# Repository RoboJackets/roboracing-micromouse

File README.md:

# Welcome to RoboRacing Micromouse
## What is Micromouse?
Micromouse is RoboRacing's primary project. Members are split into teams of 2-3 to build a brand new bot from scratch. This repository stores the code for RoboRacing's primary competitive bot. 

> Watch a detailed overview of the competition by the Veritasium YouTube Channel

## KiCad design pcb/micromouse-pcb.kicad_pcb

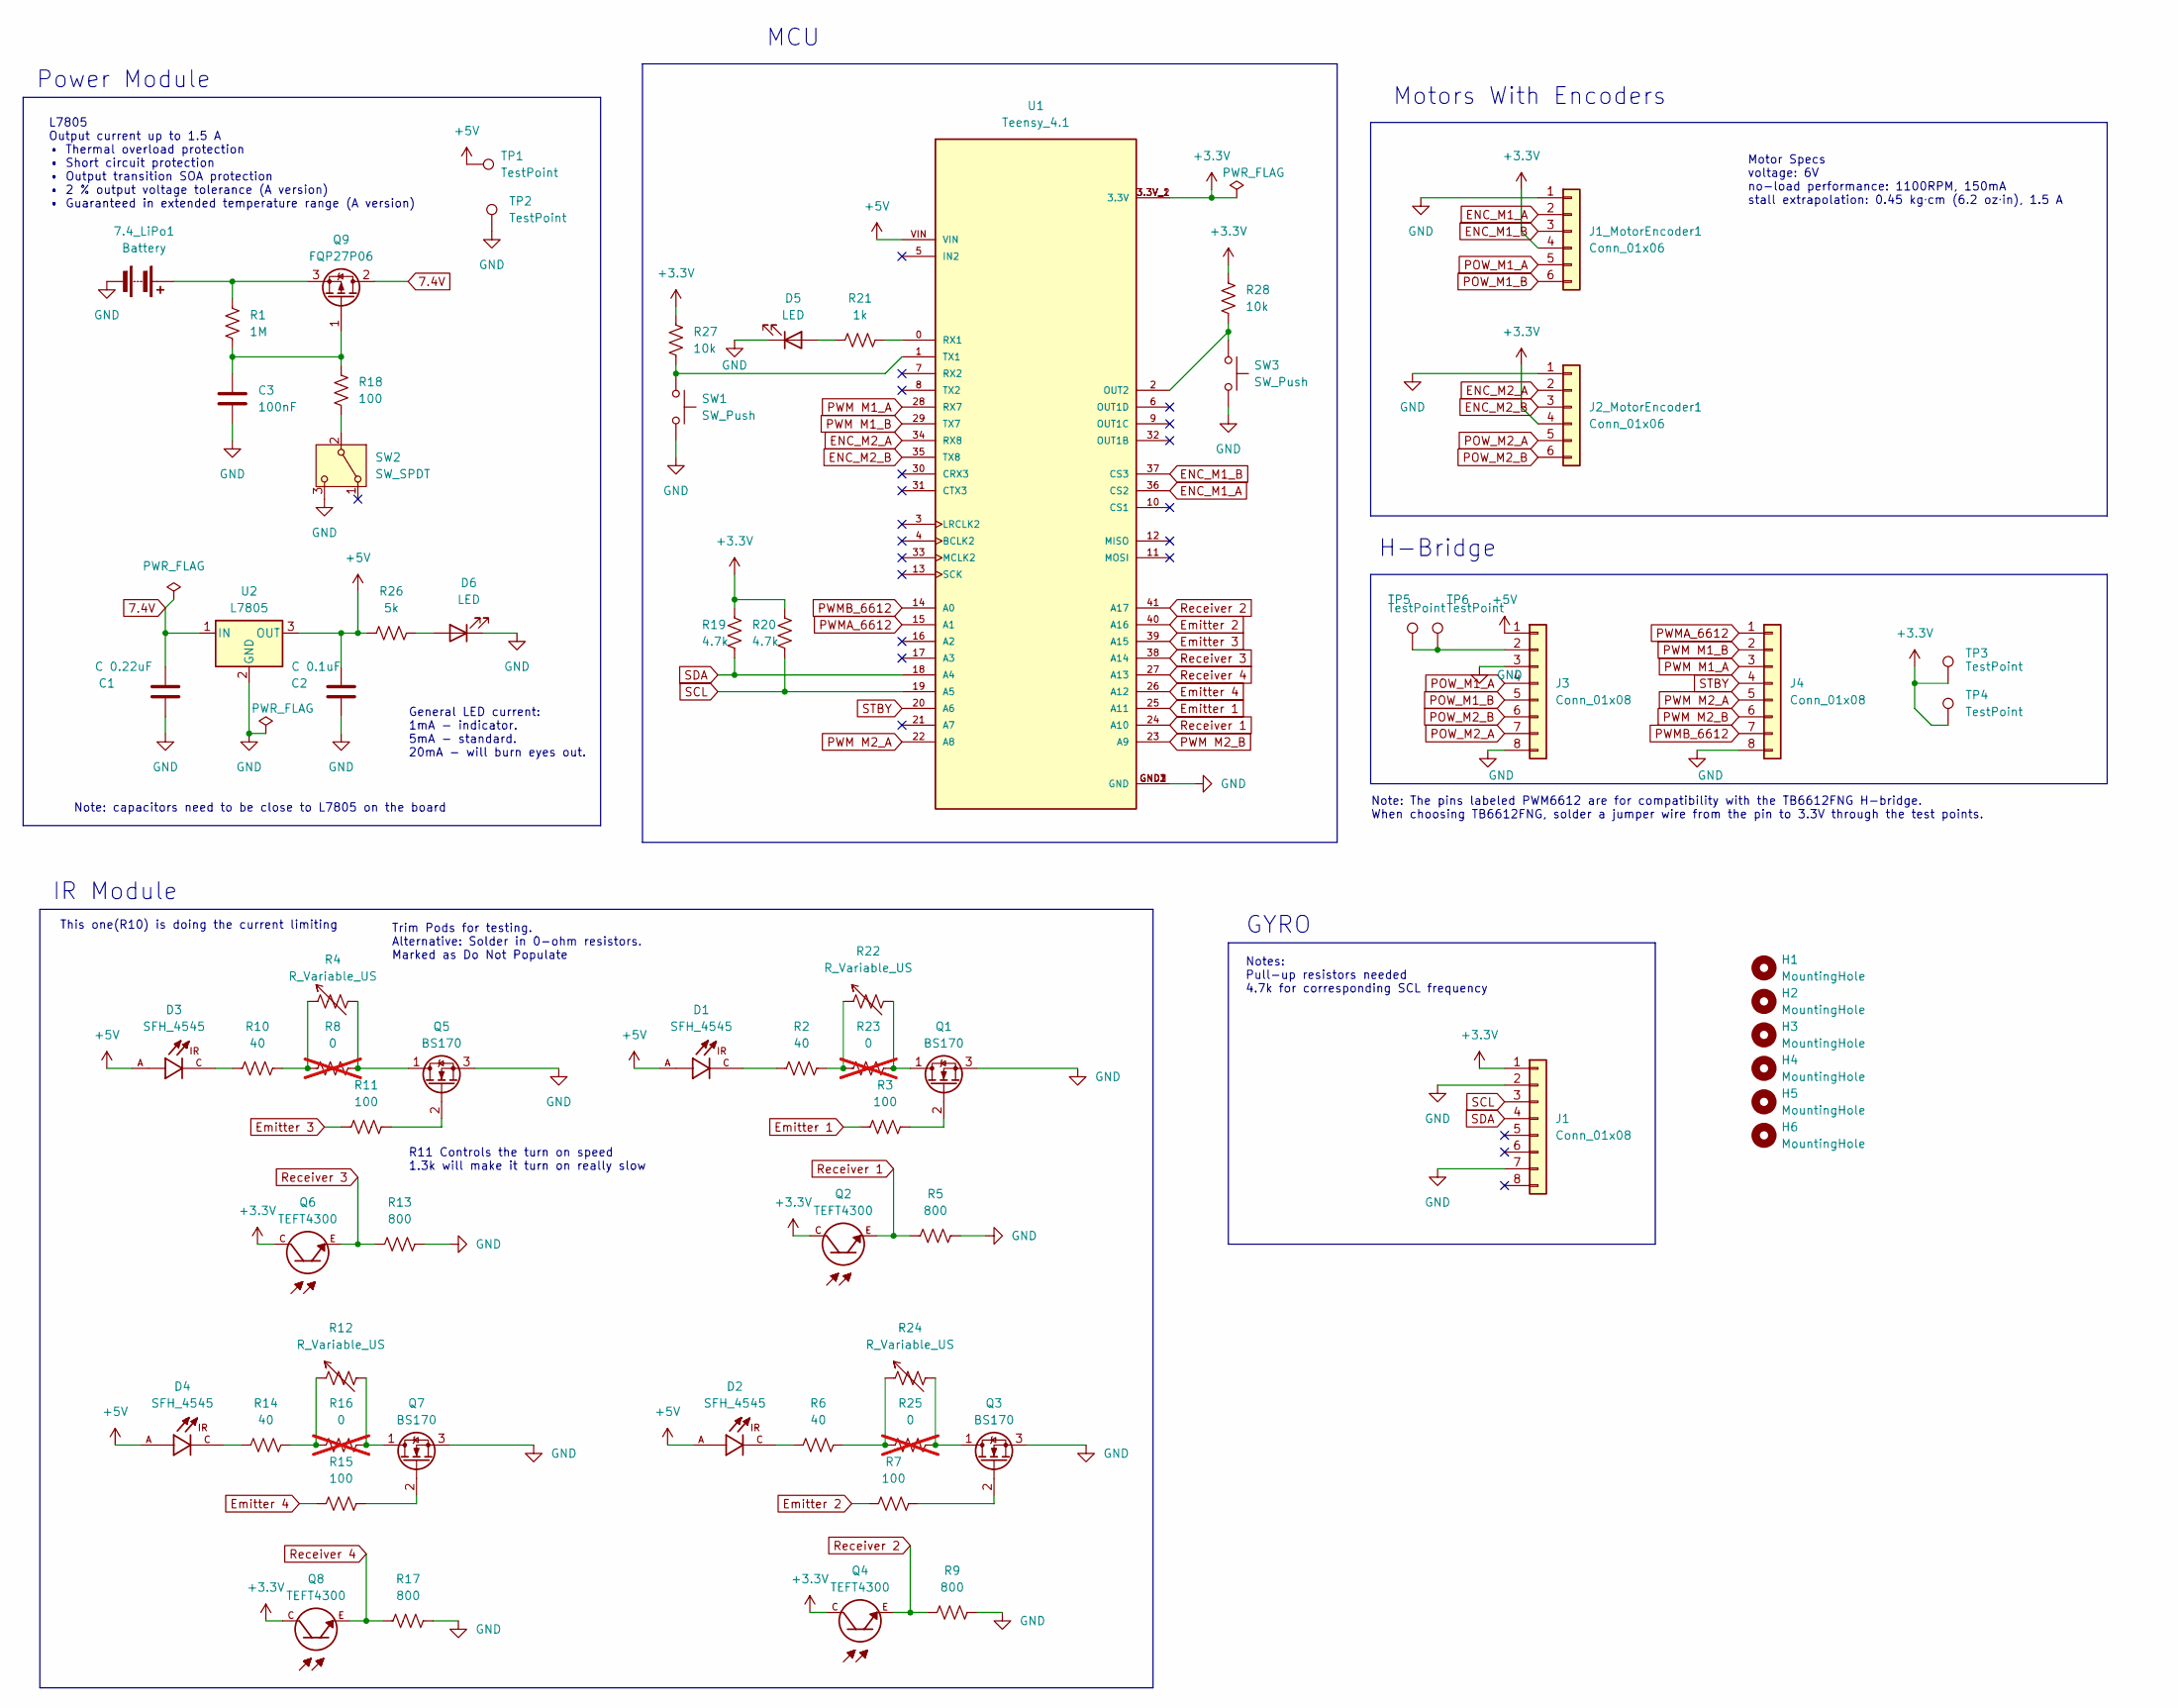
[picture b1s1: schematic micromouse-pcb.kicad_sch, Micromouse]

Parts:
7.4_LiPo1: Battery; JST_PH_B2B-PH-K_1x02_P2.00mm_Vertical
C1: C 0.22uF; C_1206_3216Metric_Pad1.33x1.80mm_HandSolder
C2: C 0.1uF; C_1206_3216Metric_Pad1.33x1.80mm_HandSolder
C3: 100nF; C_1206_3216Metric_Pad1.33x1.80mm_HandSolder
D1, D2, D3, D4: SFH_4545; DIO_SFH_4545_copy; PARTREV 1.5
D5, D6: LED; LED_1206_3216Metric_Pad1.42x1.75mm_HandSolder
H1, H2, H3, H4, H5, H6: MountingHole; MountingHole_4.3mm_M4
J1, J3, J4: Conn_01x08; PinSocket_1x08_P2.54mm_Vertical
J1_MotorEncoder1, J2_MotorEncoder1: Conn_01x06; PinSocket_1x06_P2.54mm_Vertical
Q1, Q3, Q5, Q7: BS170; TO-92_Inline
Q2, Q4, Q6, Q8: TEFT4300; XDCR_TEFT4300
Q9: FQP27P06; TO-220-3_Vertical
R1: 1M; R_1206_3216Metric_Pad1.30x1.75mm_HandSolder
R2, R6, R10, R14: 40; R_1206_3216Metric_Pad1.30x1.75mm_HandSolder
R3, R7, R11, R15, R18: 100; R_1206_3216Metric_Pad1.30x1.75mm_HandSolder
R4, R12, R22, R24: R_Variable_US; TRIM_PV36W203C01B00
R5, R9, R13, R17: 800; R_1206_3216Metric_Pad1.30x1.75mm_HandSolder
R8, R16, R23, R25: 0; R_1206_3216Metric_Pad1.30x1.75mm_HandSolder; not fitted
R19, R20: 4.7k; R_1206_3216Metric_Pad1.30x1.75mm_HandSolder
R21: 1k; R_1206_3216Metric_Pad1.30x1.75mm_HandSolder
R26: 5k; R_1206_3216Metric_Pad1.30x1.75mm_HandSolder
R27, R28: 10k; R_1206_3216Metric_Pad1.30x1.75mm_HandSolder
SW1, SW3: SW_Push; SW_SPST_B3SL-1002P
SW2: SW_SPDT; SW_Slide_SPDT_Angled_CK_OS102011MA1Q
TP1, TP2, TP3, TP4, TP5, TP6: TestPoint; TestPoint_THTPad_D2.0mm_Drill1.0mm
U1: Teensy_4.1; Teensy4.1_LessHoles; PARTREV 4.1
U2: L7805; TO-220-3_Vertical

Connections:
7.4V: C1.1, Q9.2 (D), U2.1 (IN)
+3.3V: J1.1, J1_MotorEncoder1.4, J2_MotorEncoder1.4, Q2.C, Q4.C, Q6.C, Q8.C, R19.1, R20.1, R27.1, R28.1, TP3.1, TP4.1, U1.3.3V_1 (3.3V), U1.3.3V_2 (3.3V)
+5V: C2.2, D1.A, D2.A, D3.A, D4.A, J3.1, R26.1, TP1.1, U1.VIN, U2.3 (OUT)
ENC_M1_A: J1_MotorEncoder1.2, U1.36 (CS2)
ENC_M1_B: J1_MotorEncoder1.3, U1.37 (CS3)
ENC_M2_A: J2_MotorEncoder1.2, U1.34 (RX8)
ENC_M2_B: J2_MotorEncoder1.3, U1.35 (TX8)
Emitter 1: R3.1, U1.25 (A11)
Emitter 2: R7.1, U1.40 (A16)
Emitter 3: R11.1, U1.39 (A15)
Emitter 4: R15.1, U1.26 (A12)
GND: 7.4_LiPo1.2 (-), C1.2, C2.1, C3.2, D5.1 (K), D6.1 (K), J1.2, J1.7, J1_MotorEncoder1.1, J2_MotorEncoder1.1, J3.3, J3.8, J4.8, Q1.3 (S), Q3.3 (S), Q5.3 (S), Q7.3 (S), R5.2, R9.2, R13.2, R17.2, SW1.2, SW2.3 (C), SW3.2, TP2.1, U1.GND1 (GND), U1.GND2 (GND), U1.GND3 (GND), U2.2 (GND)
unnamed: 7.4_LiPo1.1 (+), Q9.3 (S), R1.1
unnamed: D1.C, R2.1
unnamed: D2.C, R6.1
unnamed: D3.C, R10.1
unnamed: D4.C, R14.1
unnamed: D5.2 (A), R21.1
unnamed: D6.2 (A), R26.2
unnamed: J3.2, TP5.1, TP6.1
unnamed: Q1.1 (D), R22.2, R23.2
unnamed: Q1.2 (G), R3.2
unnamed: Q3.1 (D), R24.2, R25.2
unnamed: Q3.2 (G), R7.2
unnamed: Q5.1 (D), R4.2, R8.2
unnamed: Q5.2 (G), R11.2
unnamed: Q7.1 (D), R12.2, R16.2
unnamed: Q7.2 (G), R15.2
unnamed: C3.1, Q9.1 (G), R1.2, R18.1
unnamed: R2.2, R22.1, R23.1
unnamed: R4.1, R8.1, R10.2
unnamed: R12.1, R14.2, R16.1
unnamed: R6.2, R24.1, R25.1
unnamed: R18.2, SW2.2 (B)
unnamed: R28.2, SW3.1, U1.2 (OUT2)
unnamed: R21.2, U1.0 (RX1)
unnamed: R27.2, SW1.1, U1.1 (TX1)
POW_M1_A: J1_MotorEncoder1.5, J3.4
POW_M1_B: J1_MotorEncoder1.6, J3.5
POW_M2_A: J2_MotorEncoder1.5, J3.7
POW_M2_B: J2_MotorEncoder1.6, J3.6
PWM M1_A: J4.3, U1.28 (RX7)
PWM M1_B: J4.2, U1.29 (TX7)
PWM M2_A: J4.5, U1.22 (A8)
PWM M2_B: J4.6, U1.23 (A9)
PWMA_6612: J4.1, U1.15 (A1)
PWMB_6612: J4.7, U1.14 (A0)
Receiver 1: Q2.E, R5.1, U1.24 (A10)
Receiver 2: Q4.E, R9.1, U1.41 (A17)
Receiver 3: Q6.E, R13.1, U1.38 (A14)
Receiver 4: Q8.E, R17.1, U1.27 (A13)
SCL: J1.3, R20.2, U1.19 (A5)
SDA: J1.4, R19.2, U1.18 (A4)
STBY: J4.4, U1.20 (A6)

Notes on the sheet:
Trim Pods for testing. Alternative: Solder in 0-ohm resistors. Marked as Do Not Populate
Note: capacitors need to be close to L7805 on the board
General LED current: 1mA - indicator. 5mA - standard. 20mA - will burn eyes out.
GYRO
H-Bridge
This one(R10) is doing the current limiting
R11 Controls the turn on speed 1.3k will make it turn on really slow
Notes: Pull-up resistors needed 4.7k for corresponding SCL frequency
Power Module
IR Module
MCU
Motor Specs voltage: 6V no-load performance: 1100RPM, 150mA stall extrapolation: 0.45 kg⋅cm (6.2 oz⋅in), 1.5 A
Note: The pins labeled PWM6612 are for compatibility with the TB6612FNG H-bridge. When choosing TB6612FNG, solder a jumper wire from the pin to 3.3V through the test points.
Motors With Encoders
L7805 Output current up to 1.5 A • Thermal overload protection • Short circuit protection • Output transition SOA protection • 2 % output voltage tolerance (A version) • Guaranteed in extended temperature range (A version)

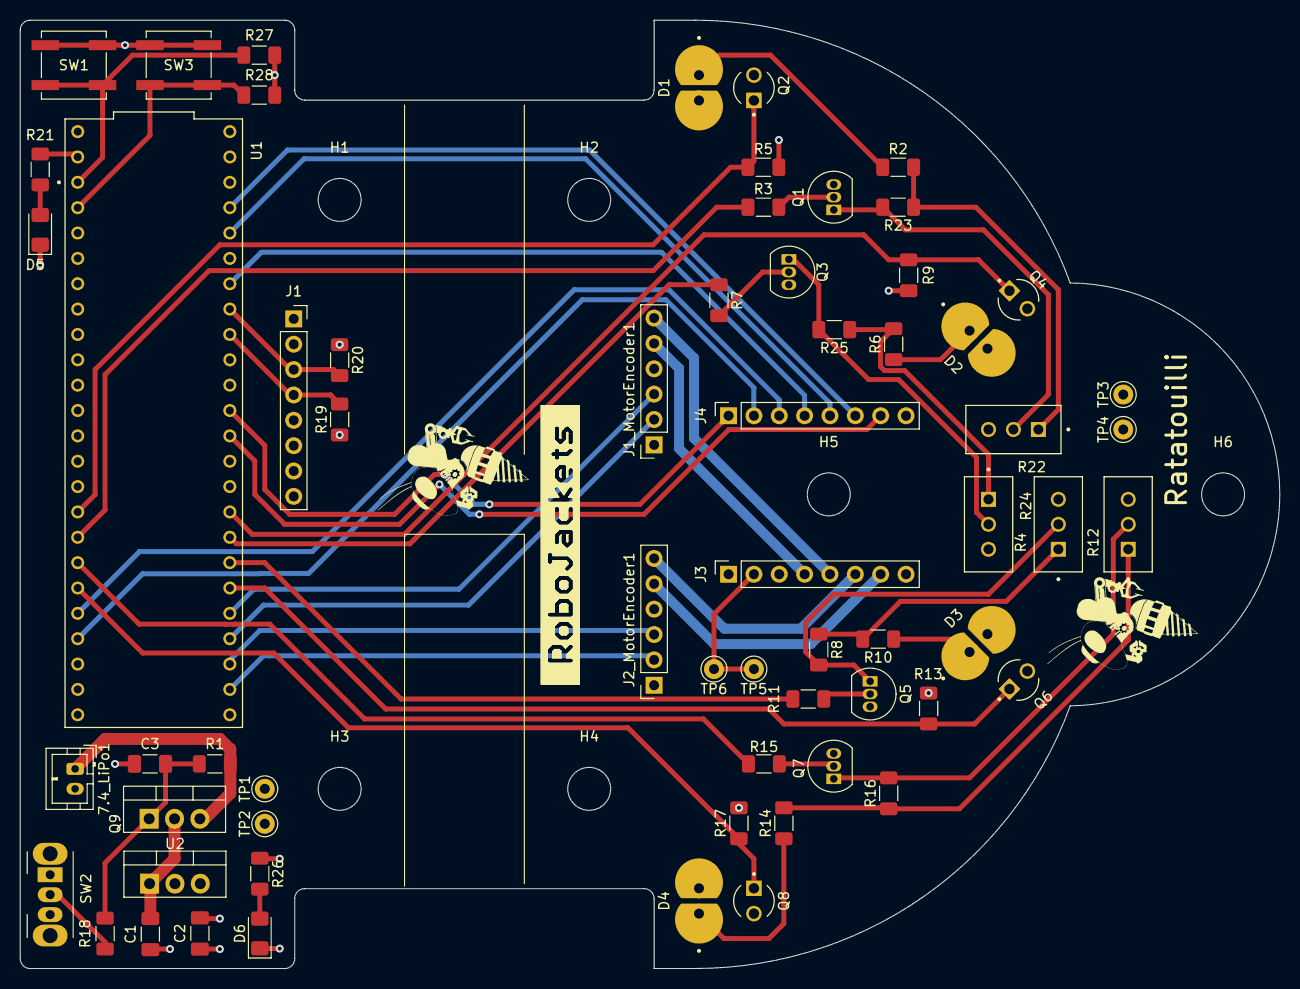
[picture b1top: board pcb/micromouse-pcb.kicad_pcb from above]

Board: 4 copper layers, 126.2 x 95.0 mm, 69 parts (0 on the bottom side), 54 nets.

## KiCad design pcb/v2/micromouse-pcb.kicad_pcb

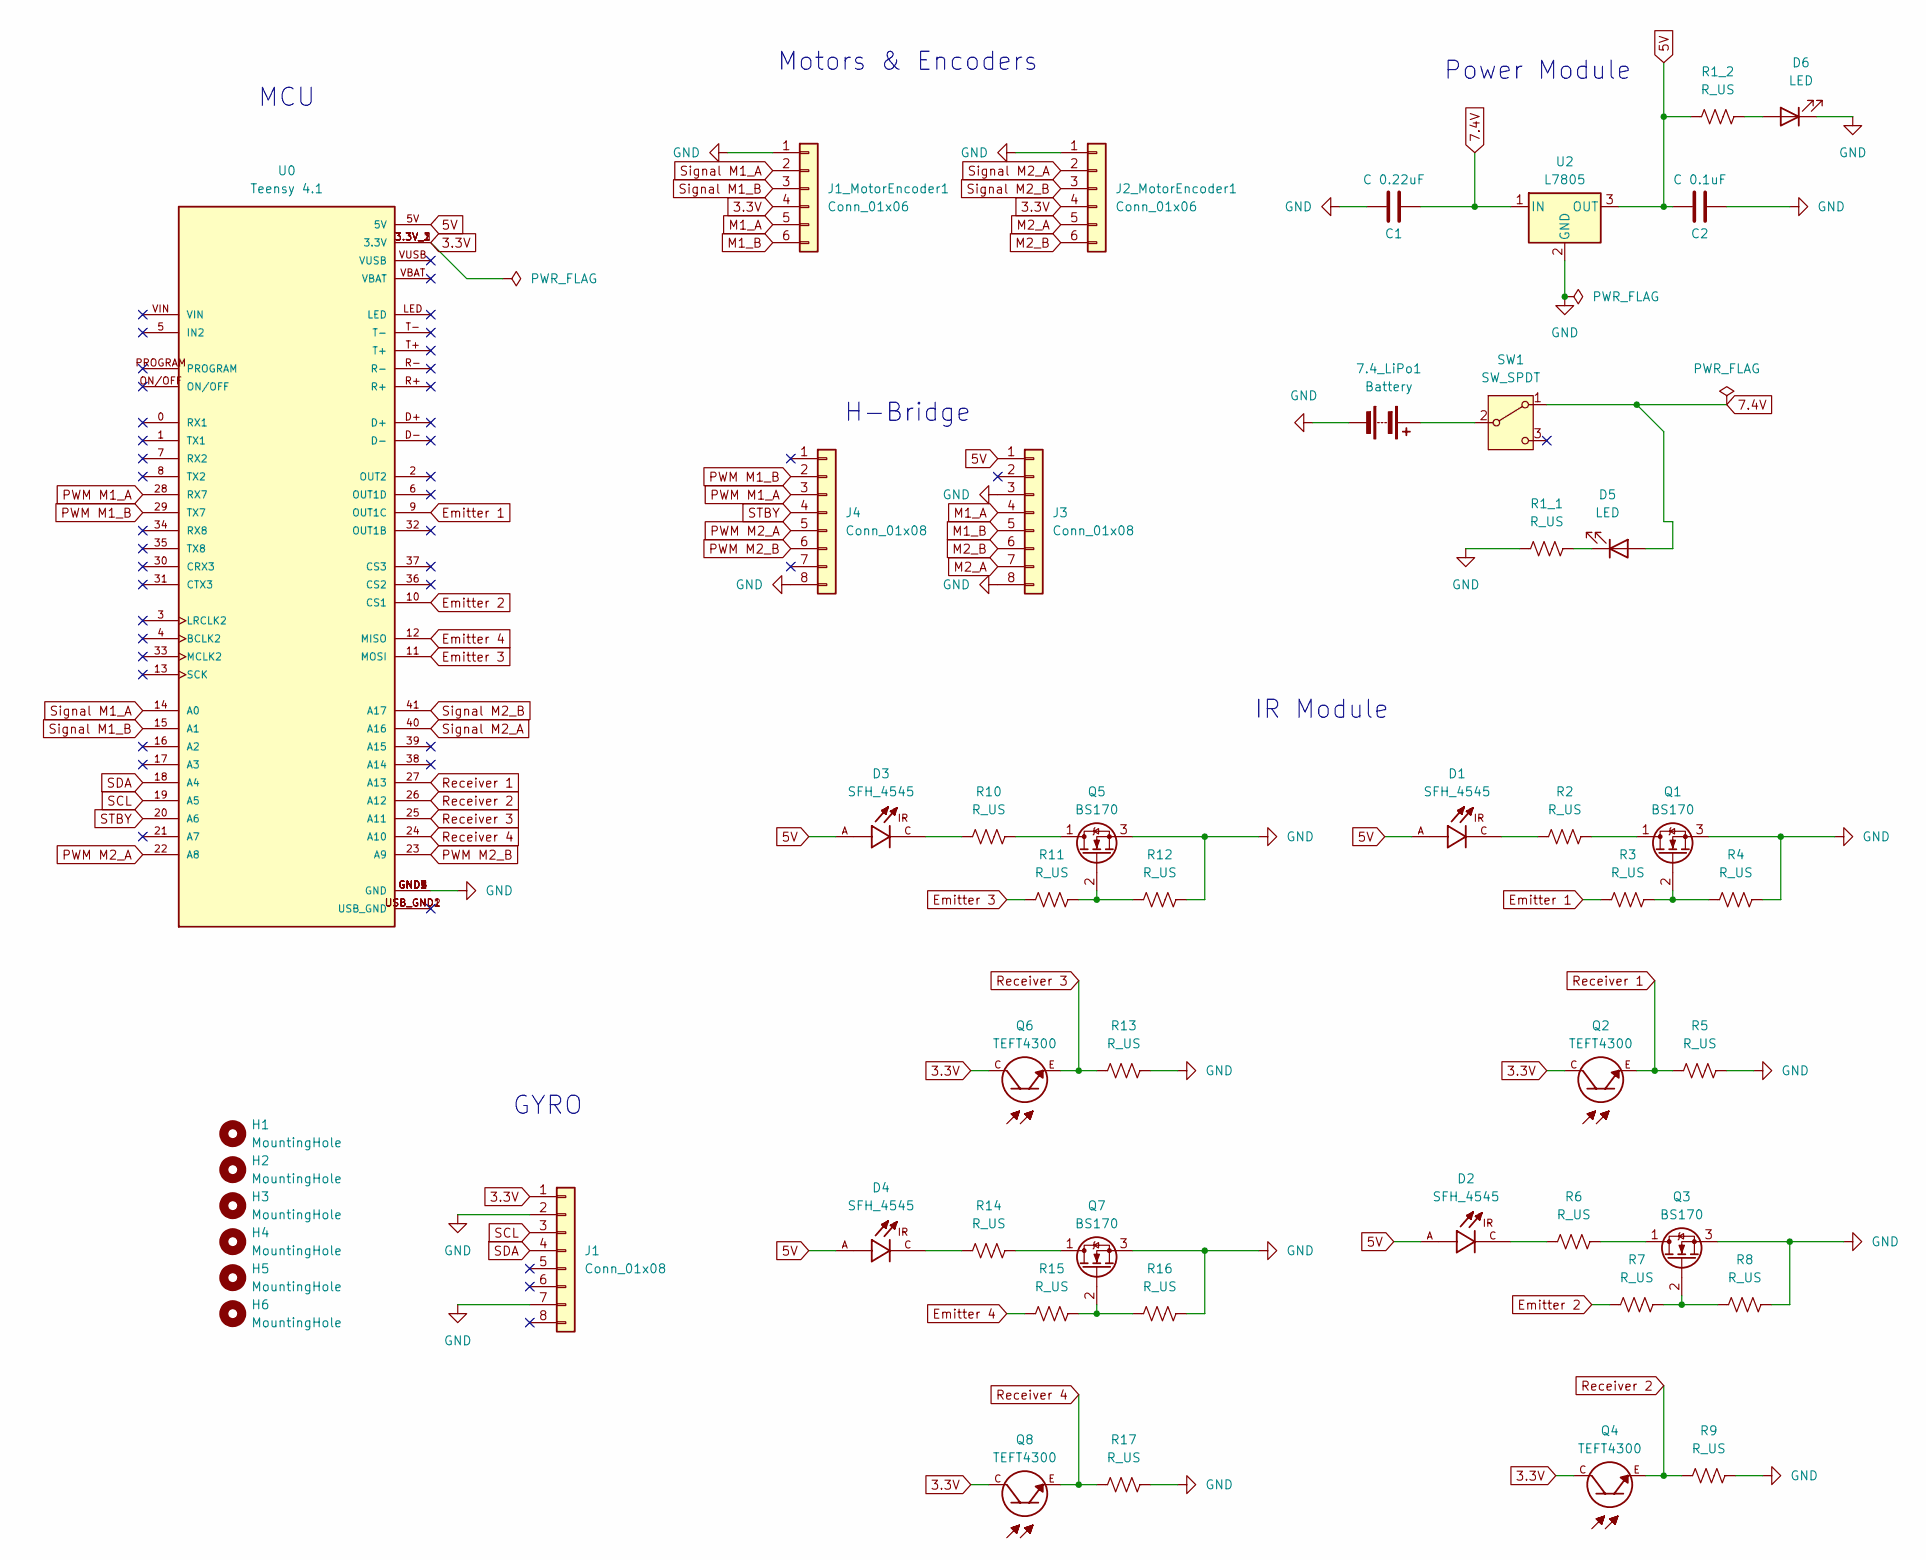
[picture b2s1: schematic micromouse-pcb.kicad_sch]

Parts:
7.4_LiPo1: Battery; PinHeader_1x02_P2.54mm_Vertical
C1: C 0.22uF; C_1206_3216Metric_Pad1.33x1.80mm_HandSolder
C2: C 0.1uF; C_1206_3216Metric_Pad1.33x1.80mm_HandSolder
D1, D2, D3, D4: SFH_4545; DIO_SFH_4545; PARTREV 1.5
D5, D6: LED; LED_D5.0mm
H1, H2, H3, H4, H5, H6: MountingHole; MountingHole_4.3mm_M4
J1, J3, J4: Conn_01x08; PinSocket_1x08_P2.54mm_Vertical
J1_MotorEncoder1, J2_MotorEncoder1: Conn_01x06; PinSocket_1x06_P2.54mm_Vertical
Q1, Q3, Q5, Q7: BS170; TO-92_Inline
Q2, Q4, Q6, Q8: TEFT4300; XDCR_TEFT4300
R1_1, R1_2, R2, R3, R4, R5, R6, R7, R8, R9, R10, R11, R12, R13, R14, R15, R16, R17: R_US; R_1206_3216Metric_Pad1.30x1.75mm_HandSolder
SW1: SW_SPDT; PinHeader_1x03_P2.54mm_Vertical
U0: Teensy 4.1; MODULE_DEV-16771; PARTREV 4.1
U2: L7805; TO-220-3_Vertical

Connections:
3.3V: J1.1, J1_MotorEncoder1.4, J2_MotorEncoder1.4, Q2.C, Q4.C, Q6.C, Q8.C, U0.3.3V_1 (3.3V), U0.3.3V_2 (3.3V), U0.3.3V_3 (3.3V)
5V: C2.1, D1.A, D2.A, D3.A, D4.A, J3.1, R1_2.1, U0.5V, U2.3 (OUT)
7.4V: C1.1, D5.2 (A), SW1.1 (A), U2.1 (IN)
Emitter 1: R3.1, U0.9 (OUT1C)
Emitter 2: R7.1, U0.10 (CS1)
Emitter 3: R11.1, U0.11 (MOSI)
Emitter 4: R15.1, U0.12 (MISO)
GND: 7.4_LiPo1.2 (-), C1.2, C2.2, D6.1 (K), J1.2, J1.7, J1_MotorEncoder1.1, J2_MotorEncoder1.1, J3.3, J3.8, J4.8, Q1.3 (S), Q3.3 (S), Q5.3 (S), Q7.3 (S), R1_1.1, R4.2, R5.2, R8.2, R9.2, R12.2, R13.2, R16.2, R17.2, U0.GND1 (GND), U0.GND2 (GND), U0.GND3 (GND), U0.GND4 (GND), U0.GND5 (GND), U2.2 (GND)
M1_A: J1_MotorEncoder1.5, J3.4
M1_B: J1_MotorEncoder1.6, J3.5
M2_A: J2_MotorEncoder1.5, J3.7
M2_B: J2_MotorEncoder1.6, J3.6
unnamed: 7.4_LiPo1.1 (+), SW1.2 (B)
unnamed: D1.C, R2.1
unnamed: D2.C, R6.1
unnamed: D3.C, R10.1
unnamed: D4.C, R14.1
unnamed: D5.1 (K), R1_1.2
unnamed: D6.2 (A), R1_2.2
unnamed: Q1.1 (D), R2.2
unnamed: Q1.2 (G), R3.2, R4.1
unnamed: Q3.1 (D), R6.2
unnamed: Q3.2 (G), R7.2, R8.1
unnamed: Q5.1 (D), R10.2
unnamed: Q5.2 (G), R11.2, R12.1
unnamed: Q7.1 (D), R14.2
unnamed: Q7.2 (G), R15.2, R16.1
PWM M1_A: J4.3, U0.28 (RX7)
PWM M1_B: J4.2, U0.29 (TX7)
PWM M2_A: J4.5, U0.22 (A8)
PWM M2_B: J4.6, U0.23 (A9)
Receiver 1: Q2.E, R5.1, U0.27 (A13)
Receiver 2: Q4.E, R9.1, U0.26 (A12)
Receiver 3: Q6.E, R13.1, U0.25 (A11)
Receiver 4: Q8.E, R17.1, U0.24 (A10)
SCL: J1.3, U0.19 (A5)
SDA: J1.4, U0.18 (A4)
STBY: J4.4, U0.20 (A6)
Signal M1_A: J1_MotorEncoder1.2, U0.14 (A0)
Signal M1_B: J1_MotorEncoder1.3, U0.15 (A1)
Signal M2_A: J2_MotorEncoder1.2, U0.40 (A16)
Signal M2_B: J2_MotorEncoder1.3, U0.41 (A17)

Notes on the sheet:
GYRO
H-Bridge
Power Module
IR Module
MCU
Motors & Encoders

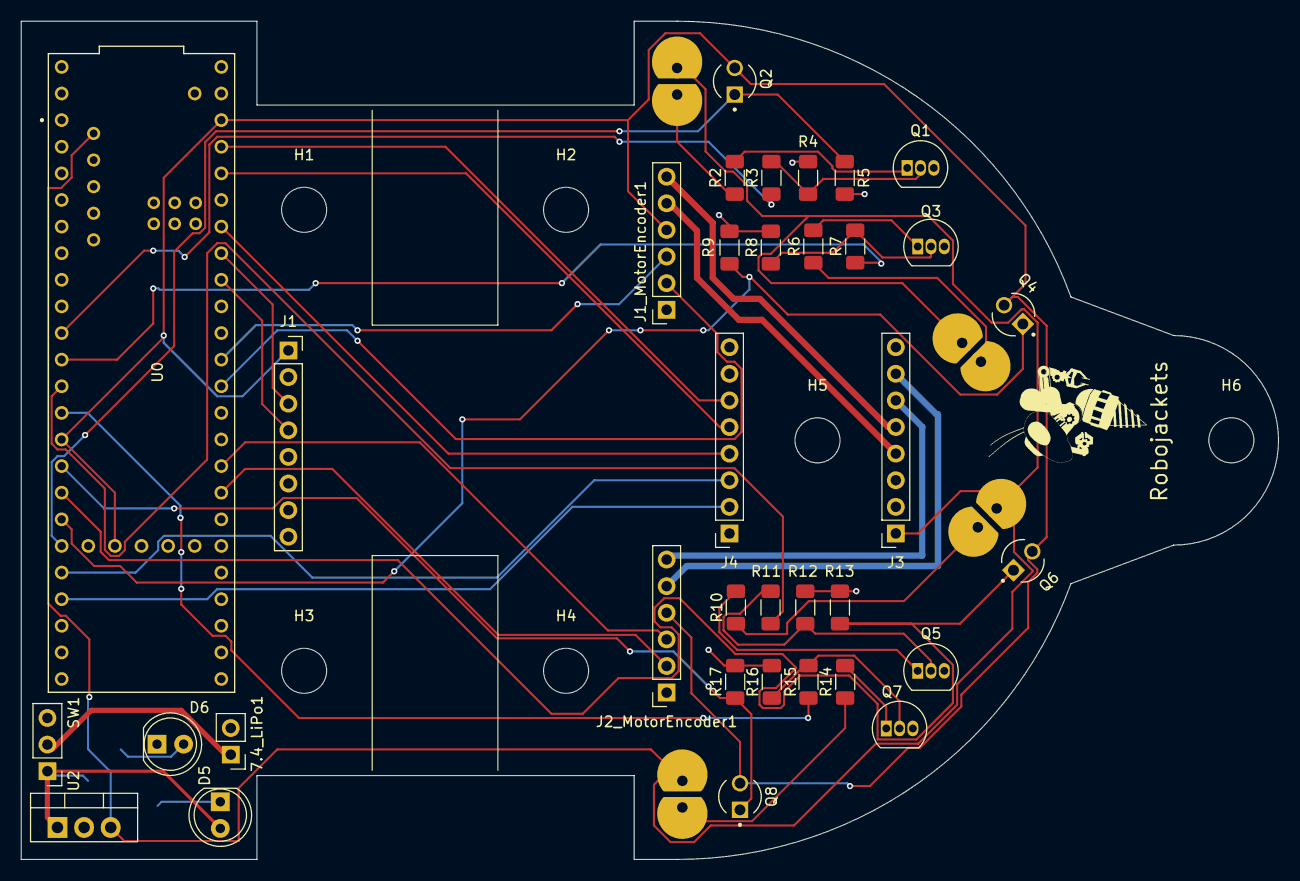
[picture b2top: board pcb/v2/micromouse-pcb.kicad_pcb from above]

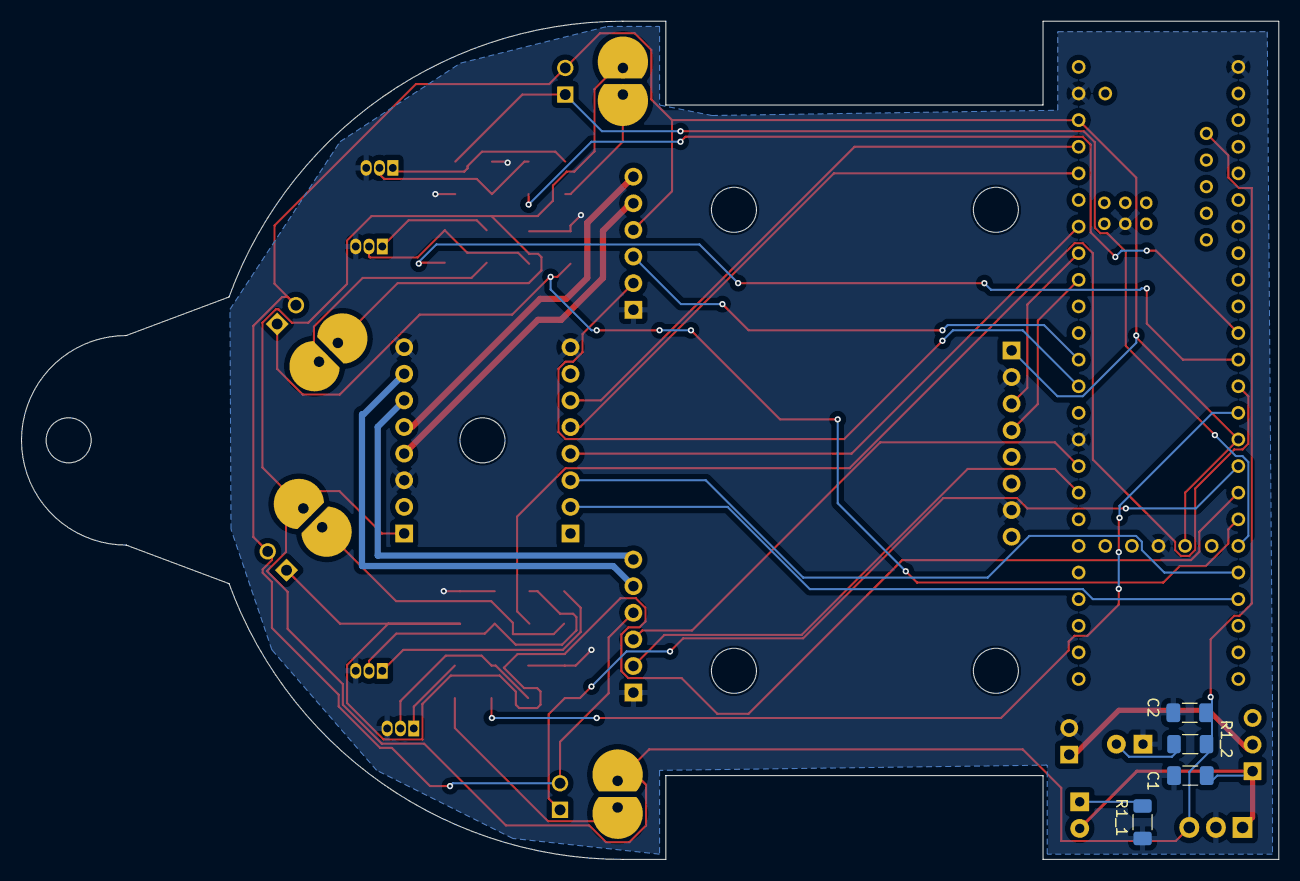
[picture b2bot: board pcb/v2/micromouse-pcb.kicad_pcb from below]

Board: 2 copper layers, 120.0 x 80.0 mm, 49 parts (4 on the bottom side), 42 nets.

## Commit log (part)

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2024-10-28 Add files via upload
    Initial commit of random maze generation for visualization and testing maze solving algorithms
    **NOTE**
    Makefile needs to be altered for different os, only set up for an Intel Mac
2024-10-29 test git
2024-10-30 Add launcher gui
2024-10-30 Add launch gui
2024-11-01 Fix A*
2024-11-11 Improve A* with priority queue and add maze generation time to console
2025-08-17 reset repo
2025-08-17 Create README.md
    init commit for new program, updating readme with basic info about whats going on
2025-08-22 Adding new submodule for algo skeleton code
2025-09-19 setup and organization
2025-09-21 flood fill start
2025-09-21 flood fill!
2025-09-21 working flood fill!
2025-09-22 organization
2025-09-22 back and forth...
2025-09-22 added .gitignore
2025-09-22 removed compiled file
2025-09-22 greedy search, but goes to 2 cells in the goal.
2025-09-22 removed extra flood fill
2025-09-22 fixed logging...
2025-09-22 removed greedy
2025-09-23 turning penalty
2025-09-23 tuned weights
2025-09-23 run ending
2025-09-23 tiebreak!
2025-09-23 tiebreaker fix!
2025-09-23 cleanup...
2025-09-23 edit
2025-09-23 logging
2025-09-25 state machine...?
2025-09-25 fully state based
2025-09-26 naming
2025-09-26 reorginization and cell selection
2025-09-27 fixes with file structure
2025-09-27 cell selection works, not ideal.
2025-09-28 removed cell selection (my idea was bad)
2025-09-28 rewrite progress, include issues
2025-09-28 fixed includes
2025-09-29 rewritten for abstract classes...
2025-09-29 pathing
2025-09-29 no dists modification
2025-09-29 fixed tiebreaker
2025-10-03 bang
2025-10-09 DFS path search
2025-10-09 removed comments
2025-10-10 comments
2025-10-12 uploaded crude beginnings of schematic and several footprints
2025-10-12 folder name change
2025-10-12 nearly working states
2025-10-12 diagonal distance fix
2025-10-13 fixed command algorithm
2025-10-13 fixed comment
2025-10-14 Init PlatformIO project
2025-10-15 Renamed folder name
2025-10-15 nearly working command based control in MMS
2025-10-15 works.!
2025-10-15 removed print
2025-10-15 new command
2025-10-18 platformio
2025-10-18 updated gitignore
2025-10-18 removed files that should not be tracked
2025-10-18 fixed platformio
2025-10-19 removed api references outside of mmsio
2025-10-19 check if mmsio
2025-10-19 return after mmsio run
2025-10-19 new needed methods
2025-10-19 Sensor stuff
2025-10-19 teensy/mms compile time switch
2025-10-19 added unimplemented teensy methods back.
2025-10-19 setup
2025-10-19 set io reference
2025-10-19 platformio builds!
2025-10-19 removed deprecated flag
2025-10-19 reading sensor states
2025-10-19 whitespace
2025-10-19 fixed reading update
2025-10-20 fixed bug
2025-10-20 added ir sensor to vector
2025-10-20 odometry with just encoders
2025-10-20 get drive speed
2025-10-20 improved update world coord
2025-10-20 grid coord
2025-10-23 prints
2025-10-24 added IR module and power module for PCB
2025-10-26 Fixing bad symbol library management
2025-10-26 recovered symbol library
2025-10-26 added Kicad to .gitignore
2025-10-27 motor module connectors
2025-10-27 changed connectors in motor module
2025-10-27 schematic not updating?
2025-10-27 Remove construction emoji from README title
2025-10-31 worked a bit on motor module
2025-11-02 finished motor module
2025-11-02 !assigned random footprints, should be revised
2025-11-03 basically done, changed a few footprints
2025-11-07 edited pcb
2025-11-14 worked on IR placement
2025-11-16 pcb design not connected yet; awaiting to be roasted in design review
2025-11-16 pid implementation
2025-11-17 increased width to 8cm, placement done
2025-11-18 PCB FINISHED
2025-11-23 re-routed PCB with B.Cu as GND layer
2025-11-23 changed board outline for ball caster mount
2025-11-24 should be version after design review
2025-11-26 fixed footprint and silkscreens
2026-01-16 wider wires?
2026-01-16 Got gyro in
2026-01-16 made motor to H-bridge wires wider
2026-01-18 Slight changes to schematic
2026-01-18 Better file paths/directories
2026-01-19 Reformatted schematic; Fixed Teensy & IR footprints; Changed Board Setups
2026-01-19 dist update
2026-01-22 end action; working h-bridge/library; sequential action
2026-01-22 yaw pid
2026-01-22 gyro lib
2026-01-22 removed lib
2026-01-23 gyro kinda works
2026-01-23 working gyro!
2026-01-25 Done placement
2026-01-25 Finished Routing!
2026-01-30 formatted; fixed includes
2026-01-30 updated resistor values on schematic
2026-01-30 seconds
2026-02-03 both motors run, one always at max speed.
2026-02-06 Added trim pots and DNP resistors
2026-02-07 progress
2026-02-08 working...?
2026-02-09 updated pcb with buttons
2026-02-09 Added robobuzz
2026-02-10 fixes to mms
2026-02-10 inital
2026-02-10 Added Ratatoulli name
2026-02-13 added action implementation back
2026-02-15 trap profile
2026-02-15 sysid
2026-02-17 velocity control
2026-02-17 fixed pid init
2026-02-17 Some stuff wrong will be fixing later
2026-02-22 updated controls; started command weights
2026-02-23 finding commands
2026-03-01 tweaks
2026-03-01 more tweaks
2026-03-01 Should work, design a lil sketch
2026-03-01 Got rid of unneccesary chat slop
2026-03-01 robot startup
2026-03-01 redone startup
2026-03-01 add first version updating maze state
2026-03-03 Conversion fixes
2026-03-03 add dir to GridCoord and fix walls
2026-03-03 centering PID
2026-03-03 circle PID
2026-03-06 Genuinely 0 progress
2026-03-06 gyro adjustments
2026-03-08 use w.theta
2026-03-08 added end condition
2026-03-08 gyro adjustment only when both sensors see
2026-03-08 clean up ir wall state code + add a grid dir function based on angle
2026-03-08 fixed ir delta
2026-03-08 remove w and l and fix update method ordering
2026-03-08 remove extra sensors
2026-03-08 fixes
2026-03-08 removed turnleft
2026-03-08 add gridRelativeCoords function and implement in maze state
2026-03-10 add basic wall avoidance function
2026-03-10 update goal
2026-03-10 adjusted formatting
2026-03-10 add taking into account past 5 readings
2026-03-10 drive straight
2026-03-14 curve action
2026-03-14 more memory fixes
2026-03-15 rolling average to IR
2026-03-15 Initial foolery
2026-03-15 logger and average values
2026-03-15 removed some prints
2026-03-15 Error findig should be done (minus tests)
2026-03-15 logger improvements
2026-03-16 No clue if this is right. On a whim and a prayer
2026-03-16 we ball???
2026-03-16 commented unused pins
2026-03-16 formatting
2026-03-16 Some math to be fixed and moved functions over
2026-03-16 pin tweaks
2026-03-19 I apologize in advance for my slop
2026-03-19 final slop
2026-03-19 chat slop
2026-03-19 progress...?
2026-03-19 fixes...?
2026-03-19 works
2026-03-19 more fixes!
2026-03-20 v tracking
2026-03-21 fixes and fixes
2026-03-21 adjustments
2026-03-21 IR tweaks
2026-03-21 Working changes UI, still not correct
2026-03-21 git ignore commit
2026-03-21 Working wall/cell detection in ui
2026-03-21 UI stuff done I think
2026-03-22 Redoing some stuff
2026-03-22 garb
2026-03-22 some tweaks
2026-03-22 better ir adjust
2026-03-22 ir adjustment fixes
2026-03-22 lots of changes
2026-03-23 almost......
2026-03-23 change
2026-03-23 stopped calling allowUpdates.
2026-03-23 tweak
2026-03-23 wfwfew
2026-03-23 zoom zoom
2026-03-23 meow
2026-03-23 fixy fix
2026-03-23 button
2026-03-23 invert
2026-03-23 meow!
2026-03-23 tweaked speeds
2026-03-23 no stop
2026-03-23 baifb
2026-03-23 push
2026-03-23 qoidhq
2026-03-23 debug
2026-03-23 argh
2026-03-23 twea
2026-03-23 thresh
2026-03-23 iuhyo
2026-03-23 testing
2026-04-06 fix fastpath stopping
